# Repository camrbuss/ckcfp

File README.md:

# ckcfp
Custom KiCad Footprints

## KiCad Environment Variables
Set `CKCFP_HOME` to the location of this repository

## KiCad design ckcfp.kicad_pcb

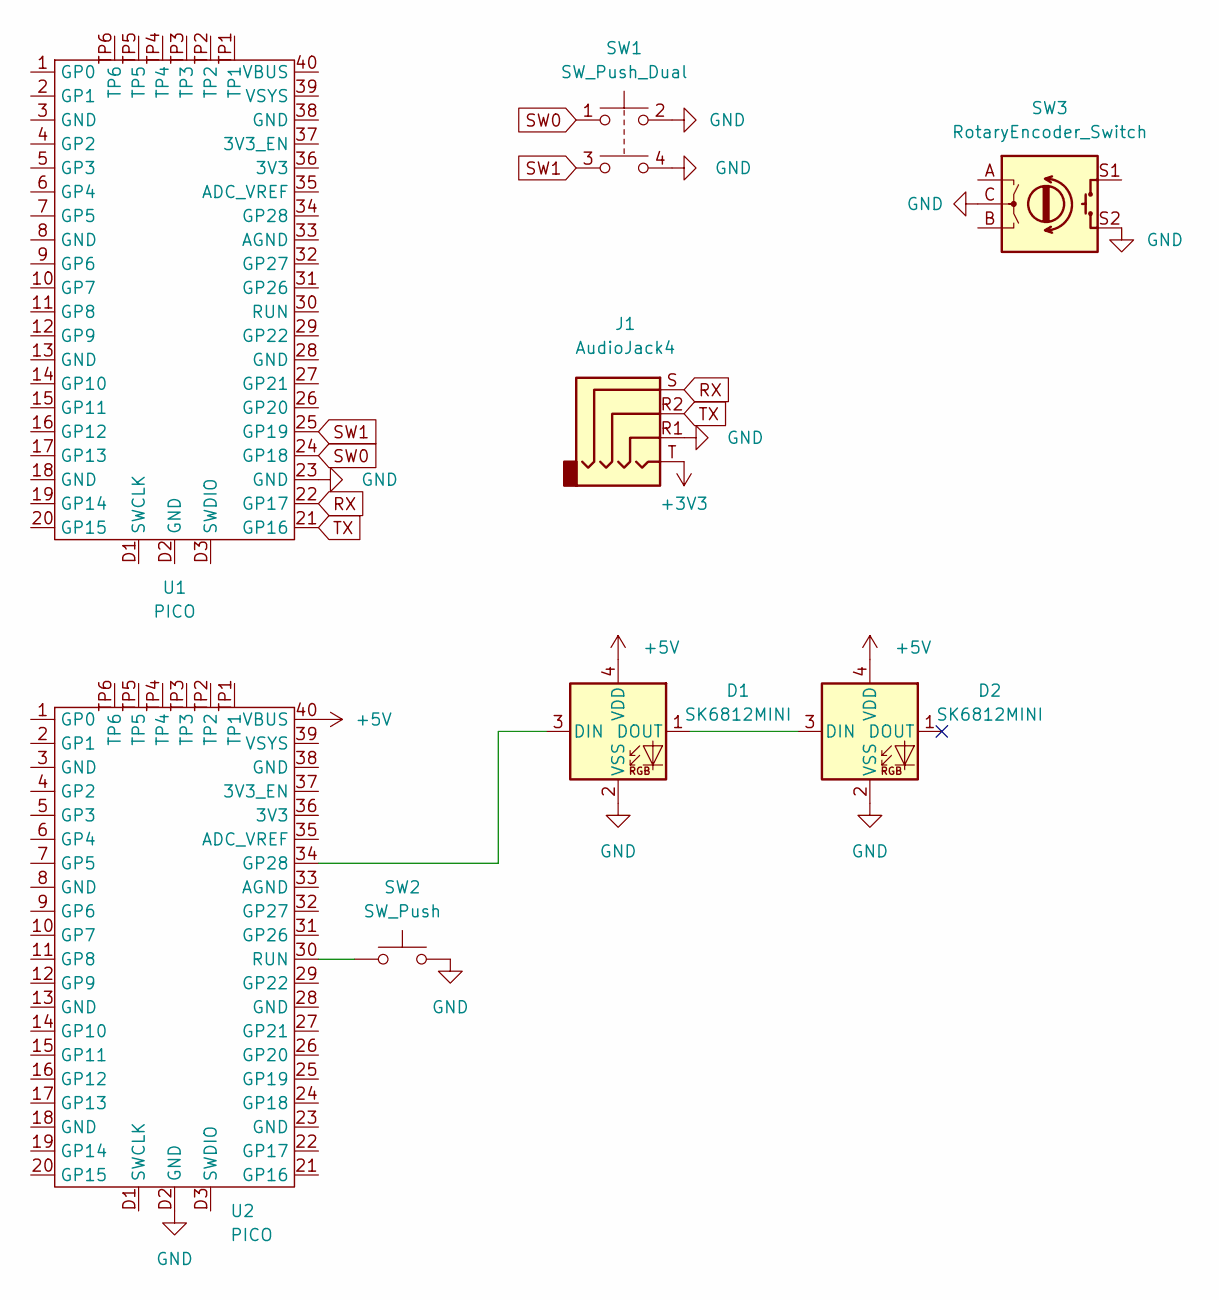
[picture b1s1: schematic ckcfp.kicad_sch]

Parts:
D1, D2: SK6812MINI; SK6812MINI_E
J1: AudioJack4; TRRS_Socket_54-00177
SW1: SW_Push_Dual; Kailh_PG1232
SW2: SW_Push; pts526_sm15_smtr2_lfs
SW3: RotaryEncoder_Switch; PEC11R_4220F_S0024
U1: PICO; raspberrypi_pico
U2: PICO; raspberrypi_pico_tht

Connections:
+3V3: J1.T
+5V: D1.4 (VDD), D2.4 (VDD), U2.40 (VBUS)
GND: D1.2 (VSS), D2.2 (VSS), J1.R1, SW1.2, SW1.4, SW2.2, SW3.C, SW3.S2, U1.23 (GND), U2.D2 (GND)
unnamed: D1.1 (DOUT), D2.3 (DIN)
unnamed: D1.3 (DIN), U2.34 (GP28)
unnamed: SW2.1, U2.30 (RUN)
RX: J1.S, U1.22 (GP17)
SW0: SW1.1, U1.24 (GP18)
SW1: SW1.3, U1.25 (GP19)
TX: J1.R2, U1.21 (GP16)

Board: 2 copper layers, 8 parts (0 on the bottom side), 9 nets, no tracks yet.

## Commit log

2021-08-07 switches, modules, connectors added
2021-08-08 3d model download script
2021-08-09 keepout regions
2021-08-16 mounting holes
2021-08-19 NPTH clearance added
2023-02-19 Add pico tht footprint
2023-02-19 Add pts526 switch footprint
2023-02-19 renamed libs to be prefixed with ckcfp
2023-02-19 add graphics library
2023-02-19 sk6812mini_e added
2023-02-20 3D model path corrections
